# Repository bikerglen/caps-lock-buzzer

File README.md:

# The Annoying CAPS LOCk Buzzer

More information is available on my personal blog:

First Version (as shown in the Keysight Labs video):

https://bikerglen.com/blog/the-annoying-caps-lock-warning-buzzer/

Second version with some minor updates:

https://bikerglen.com/blog/updates-to-the-annoying-caps-lock-warning-buzzer/

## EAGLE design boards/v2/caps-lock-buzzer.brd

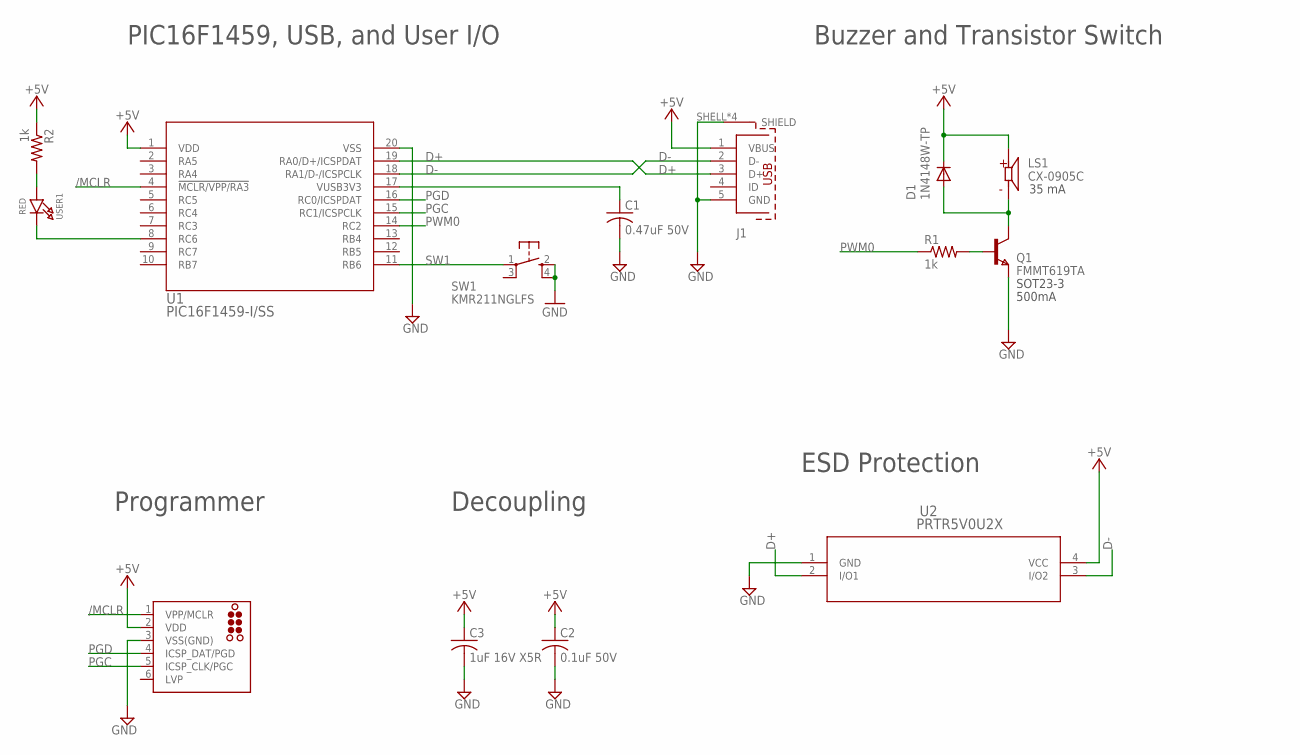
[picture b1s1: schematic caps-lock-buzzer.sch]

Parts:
C1: 0.47uF 50V; C1206K; MFR_PART_NO C1206C474K5RACTU
C2: 0.1uF 50V; C1206K; MFR_PART_NO C1206S104M5RACTU
C3: 1uF 16V X5R; C1210; MFR_PART_NO C1210C105K4PACTU
D1: 1N4148W-TP; SOD123
J1: 629105136821
J3: TC2030-MCP-NL
LS1: CX-0905C; CUI_CX-0905C
Q1: FMMT619TA; SOT-23
R1, R2: 1k; R0805
SW1: KMR211NGLFS; KMR2
U1: PIC16F1459-I/SS; SSOP20_MC
U2: PRTR5V0U2X; SOT143B
USER1: RED; CHIPLED_0805_NOOUTLINE

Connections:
+5V: C2.1, C3.1, D1.C, J1.1 (VBUS), J3.2 (VDD), LS1.P, R2.1, U1.1 (VDD), U2.4 (VCC)
/MCLR: J3.1 (VPP/MCLR), U1.4 (!MCLR/VPP/RA3)
D+: J1.3 (D+), U1.19 (RA0/D+/ICSPDAT), U2.2 (I/O1)
D-: J1.2 (D-), U1.18 (RA1/D-/ICSPCLK), U2.3 (I/O2)
GND: C1.2, C2.2, C3.2, J1.5 (GND), J1.SHELL (SHIELD), J1.SHELL1 (SHIELD), J1.SHELL2 (SHIELD), J1.SHELL3 (SHIELD), J3.3 (VSS(GND)), Q1.2 (E), SW1.2 (S), SW1.4 (S1), U1.20 (VSS), U2.1 (GND)
unnamed: R2.2, USER1.A
unnamed: U1.8 (RC6), USER1.C
unnamed: Q1.3 (B), R1.2
OUT0: D1.A, LS1.N, Q1.1 (C)
PGC: J3.5 (ICSP_CLK/PGC), U1.15 (RC1/ICSPCLK)
PGD: J3.4 (ICSP_DAT/PGD), U1.16 (RC0/ICSPDAT)
PWM0: R1.1, U1.14 (RC2)
SW1: SW1.1, U1.11 (RB6)
VUSB: C1.1, U1.17 (VUSB3V3)

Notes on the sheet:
SOT23-3
500mA
PIC16F1459, USB, and User I/O
Buzzer and Transistor Switch
Programmer
Decoupling
35 mA
ESD Protection

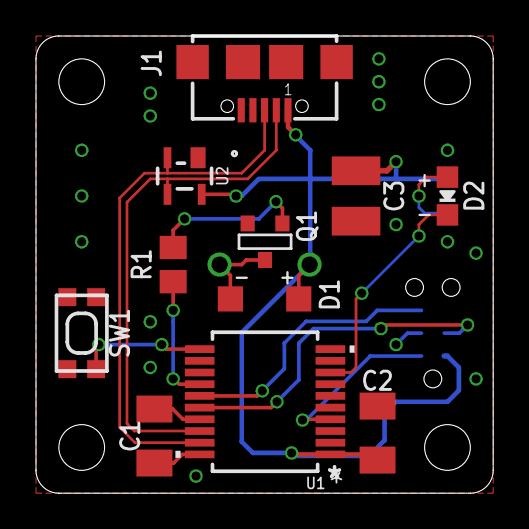
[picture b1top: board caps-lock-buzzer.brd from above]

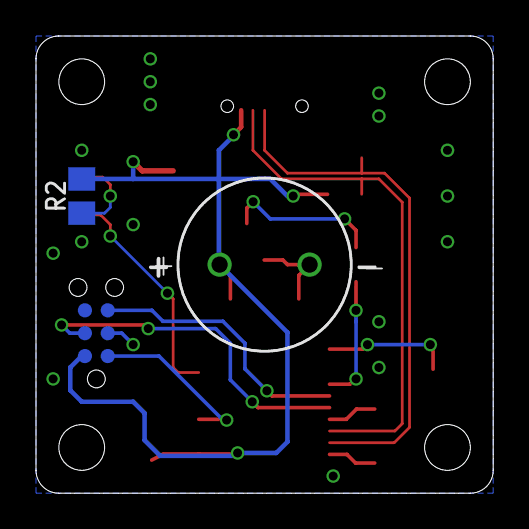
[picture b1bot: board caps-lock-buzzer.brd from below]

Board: 2 copper layers, 25.4 x 25.4 mm, 14 parts (3 on the bottom side), 14 nets.

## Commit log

2019-09-10 added boards, enclosure, and software
2019-09-14 Cleaned up for video
2019-09-29 Added v2 boards with ESD, button, and LED.
2019-09-29 Fixed LED resistor value.
2019-09-29 Added BOMs with extra parts needed for v2 version of board.
2019-09-30 added v2 stl for enclosure
2019-09-30 added zip file with usb bootloader project and source
2019-09-30 added bootloader version of buzzer firmware
2019-09-30 added Fusion 360 archive of enclosure
2019-11-06 Update README.md
    added links to personal blog post with more information on project

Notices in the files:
parts and their libraries:
InputOutputIO: Copyright: Würth Elektronik
tag-connect: ©2009 ROFA.cz - modified and updated by Robert Darlington ‹rdarlington@gmail.com›
microbuilder: This work is placed in the public domain, and may be freely used for commercial and non-commercial work with the following conditions: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
